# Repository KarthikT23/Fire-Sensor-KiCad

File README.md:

# Fire-Sensor-KiCad
Fire Sensor - 3rd PCB Design

# Schematic 

# PCB
F.Cu layer

B.Cu layer

# 3D View

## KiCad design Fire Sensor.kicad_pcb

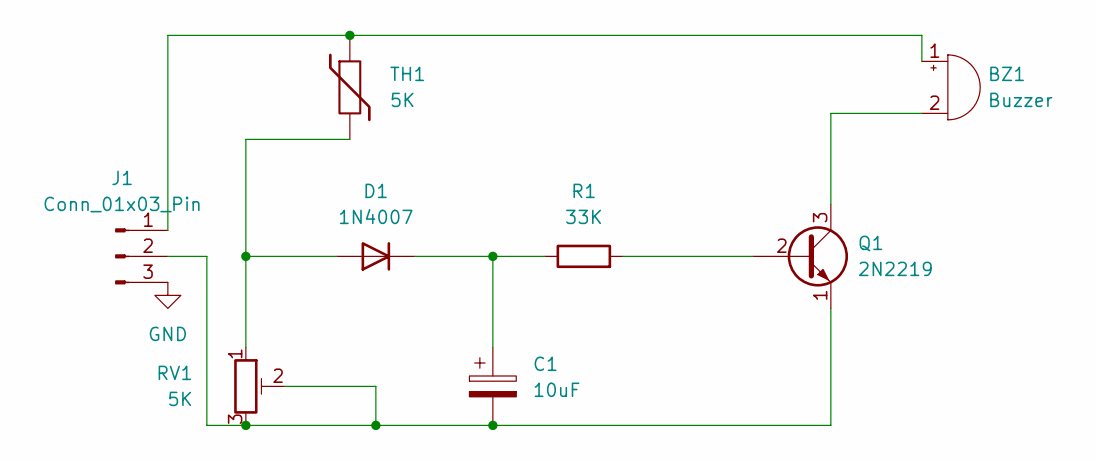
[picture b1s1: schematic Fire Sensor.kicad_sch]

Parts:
BZ1: Buzzer; Buzzer_12x9.5RM7.6
C1: 10uF; CP_Radial_D10.0mm_P3.50mm
D1: 1N4007; D_5KP_P10.16mm_Horizontal
J1: Conn_01x03_Pin; PinSocket_1x03_P2.00mm_Vertical_SMD_Pin1Right
Q1: 2N2219; TO-39-3
R1: 33K; R_Axial_DIN0411_L9.9mm_D3.6mm_P12.70mm_Horizontal
RV1: 5K; Potentiometer_ACP_CA6-H2,5_Horizontal
TH1: 5K; PinHeader_1x02_P2.00mm_Vertical

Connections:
GND: J1.3
unnamed: BZ1.2 (+), Q1.3 (C)
unnamed: BZ1.1 (-), J1.1, TH1.1
unnamed: D1.2 (A), RV1.1, TH1.2
unnamed: C1.1, D1.1 (K), R1.1
unnamed: C1.2, J1.2, Q1.1 (E), RV1.2, RV1.3
unnamed: Q1.2 (B), R1.2

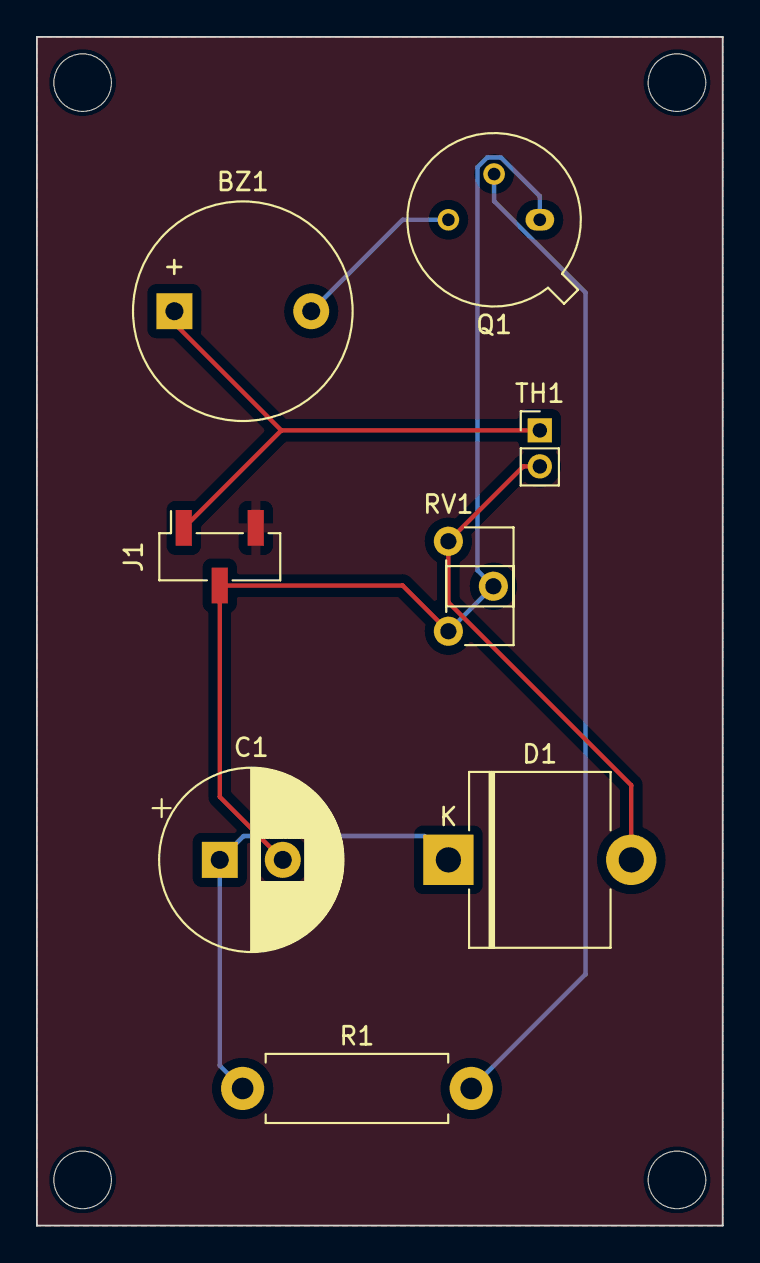
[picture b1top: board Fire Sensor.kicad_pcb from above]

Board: 2 copper layers, 38.1 x 66.0 mm, 8 parts (0 on the bottom side), 6 nets.
